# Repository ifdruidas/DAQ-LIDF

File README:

EN-EN
Hello my name is ifdruidas, I'm an electrical engineering student currently, Feb/2023, this project was a hobby of mine that ended up evolving into an article, I deliver as DAQ-LIDF, but it will always be Maria, Remote Instrument Acquisition Method, this name makes more sense in my language.

PT-BR
Ola meu nome e ifdruidas, sou um estudante de engenharia eletrica atualmente, fev/2023, esse projeto foi um passatempo meu que acabou evoluindo para um artigo, entrego como DAQ-LIDF, mas sempre sera Maria, Metodo de Aquisição Remoto de Instrumentos, esse nome faz mais sentido em meu idioma.

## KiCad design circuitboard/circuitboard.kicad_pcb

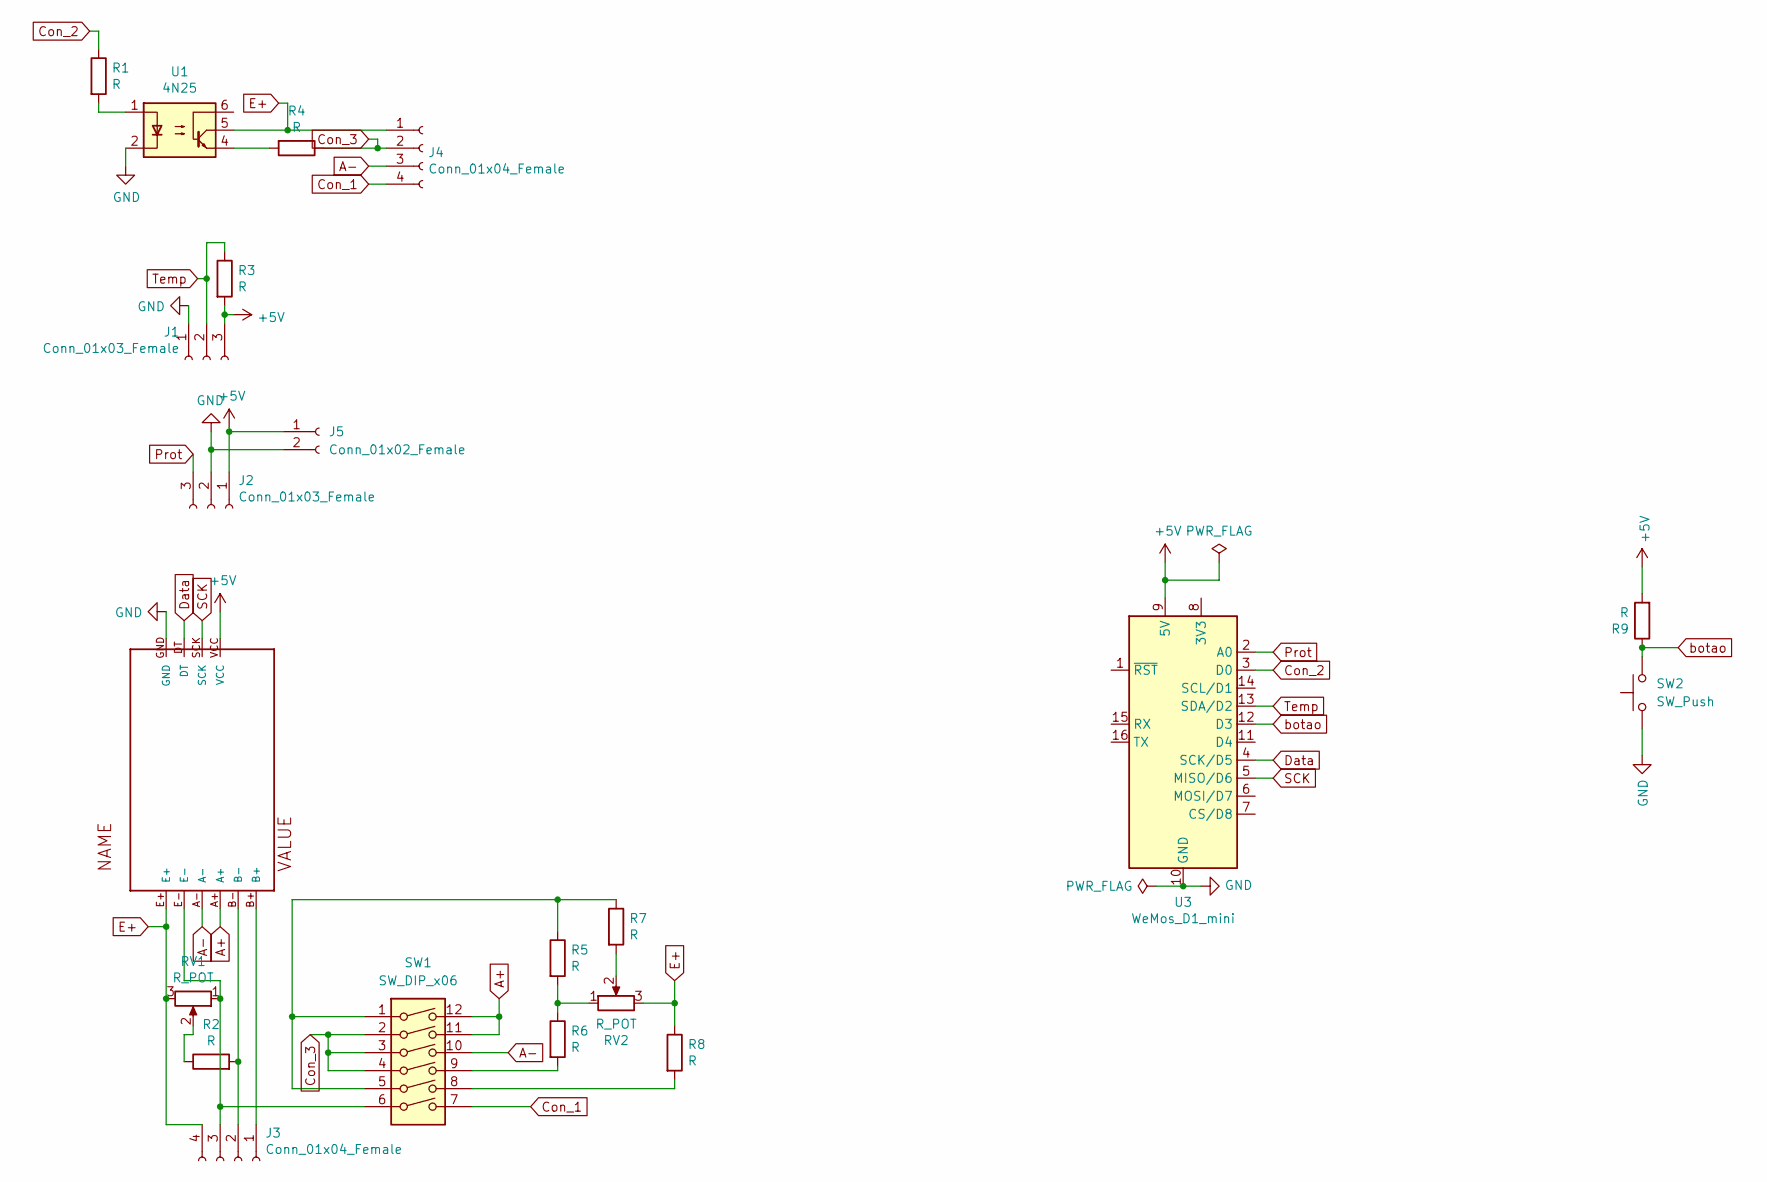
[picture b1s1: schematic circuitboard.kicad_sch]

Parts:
J1, J2: Conn_01x03_Female; PhoenixContact_MCV_1,5_3-G-5.08_1x03_P5.08mm_Vertical
J3, J4: Conn_01x04_Female; PhoenixContact_MCV_1,5_4-G-5.08_1x04_P5.08mm_Vertical
J5: Conn_01x02_Female; BarrelJack_Horizontal
R1, R2, R3, R4, R5, R6, R7, R8, R9: R; R_Axial_DIN0207_L6.3mm_D2.5mm_P10.16mm_Horizontal
RV1, RV2: R_POT; Potentiometer_Bourns_3266Y_Vertical
SW1: SW_DIP_x06; SW_DIP_SPSTx06_Slide_9.78x17.42mm_W7.62mm_P2.54mm
SW2: SW_Push; SW_PUSH_6mm
U1: 4N25; DIP-6_W7.62mm
U2: HX711
U3: WeMos_D1_mini; WEMOS_D1_mini_light

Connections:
+5V: J1.3, J2.1, J5.1, R3.2, R9.2, U2.VCC, U3.9 (5V)
A+: SW1.11, SW1.12, U2.A+
A-: J4.3, SW1.10, U2.A-
Con_1: J4.4, SW1.7
Con_2: R1.1, U3.3 (D0)
Con_3: J4.2, R4.1, SW1.2, SW1.3, SW1.4
Data: U2.DT, U3.4 (SCK/D5)
E+: J3.4, J4.1, R8.1, RV1.3, RV2.3, U1.5, U2.E+
GND: J1.1, J2.2, J5.2, SW2.1, U1.2, U2.GND, U3.10 (GND)
unnamed: J3.1, U2.B+
unnamed: J3.2, R2.2, U2.B-
unnamed: J3.3, RV1.1, SW1.6, U2.E-
unnamed: R1.2, U1.1
unnamed: R2.1, RV1.2
unnamed: R4.2, U1.4
unnamed: R5.1, R7.1, SW1.1, SW1.5
unnamed: R5.2, R6.1, RV2.1
unnamed: R6.2, SW1.9
unnamed: R7.2, RV2.2
unnamed: R8.2, SW1.8
Prot: J2.3, U3.2 (A0)
SCK: U2.SCK, U3.5 (MISO/D6)
Temp: J1.2, R3.1, U3.13 (SDA/D2)
botao: R9.1, SW2.2, U3.12 (D3)

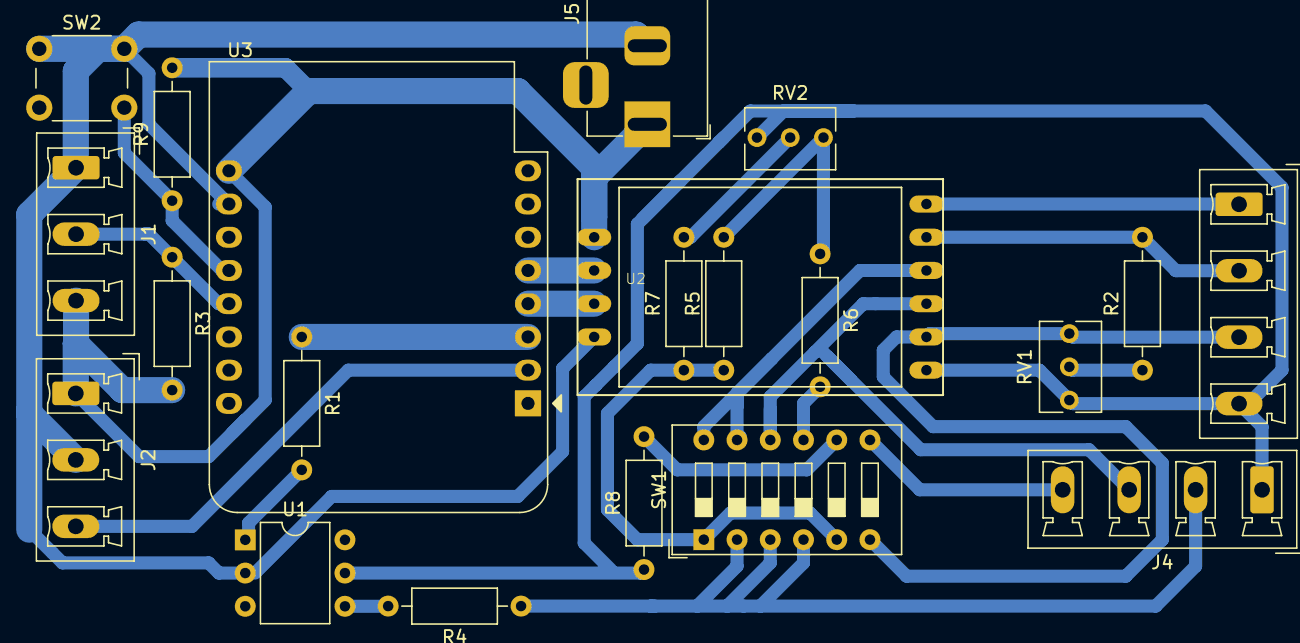
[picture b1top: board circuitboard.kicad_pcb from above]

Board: 2 copper layers, 21 parts (0 on the bottom side), 24 nets.

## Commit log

2023-02-08 DAQ-LIDF
    Hello, my name is Ifruidas, this project is a hobby, and the original name is MARIA, I leave this information for future references
